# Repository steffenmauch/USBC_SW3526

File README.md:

# USBC_SW3526
ISMARTWARE SW3526 - USB-C PD Charger with I2C interface

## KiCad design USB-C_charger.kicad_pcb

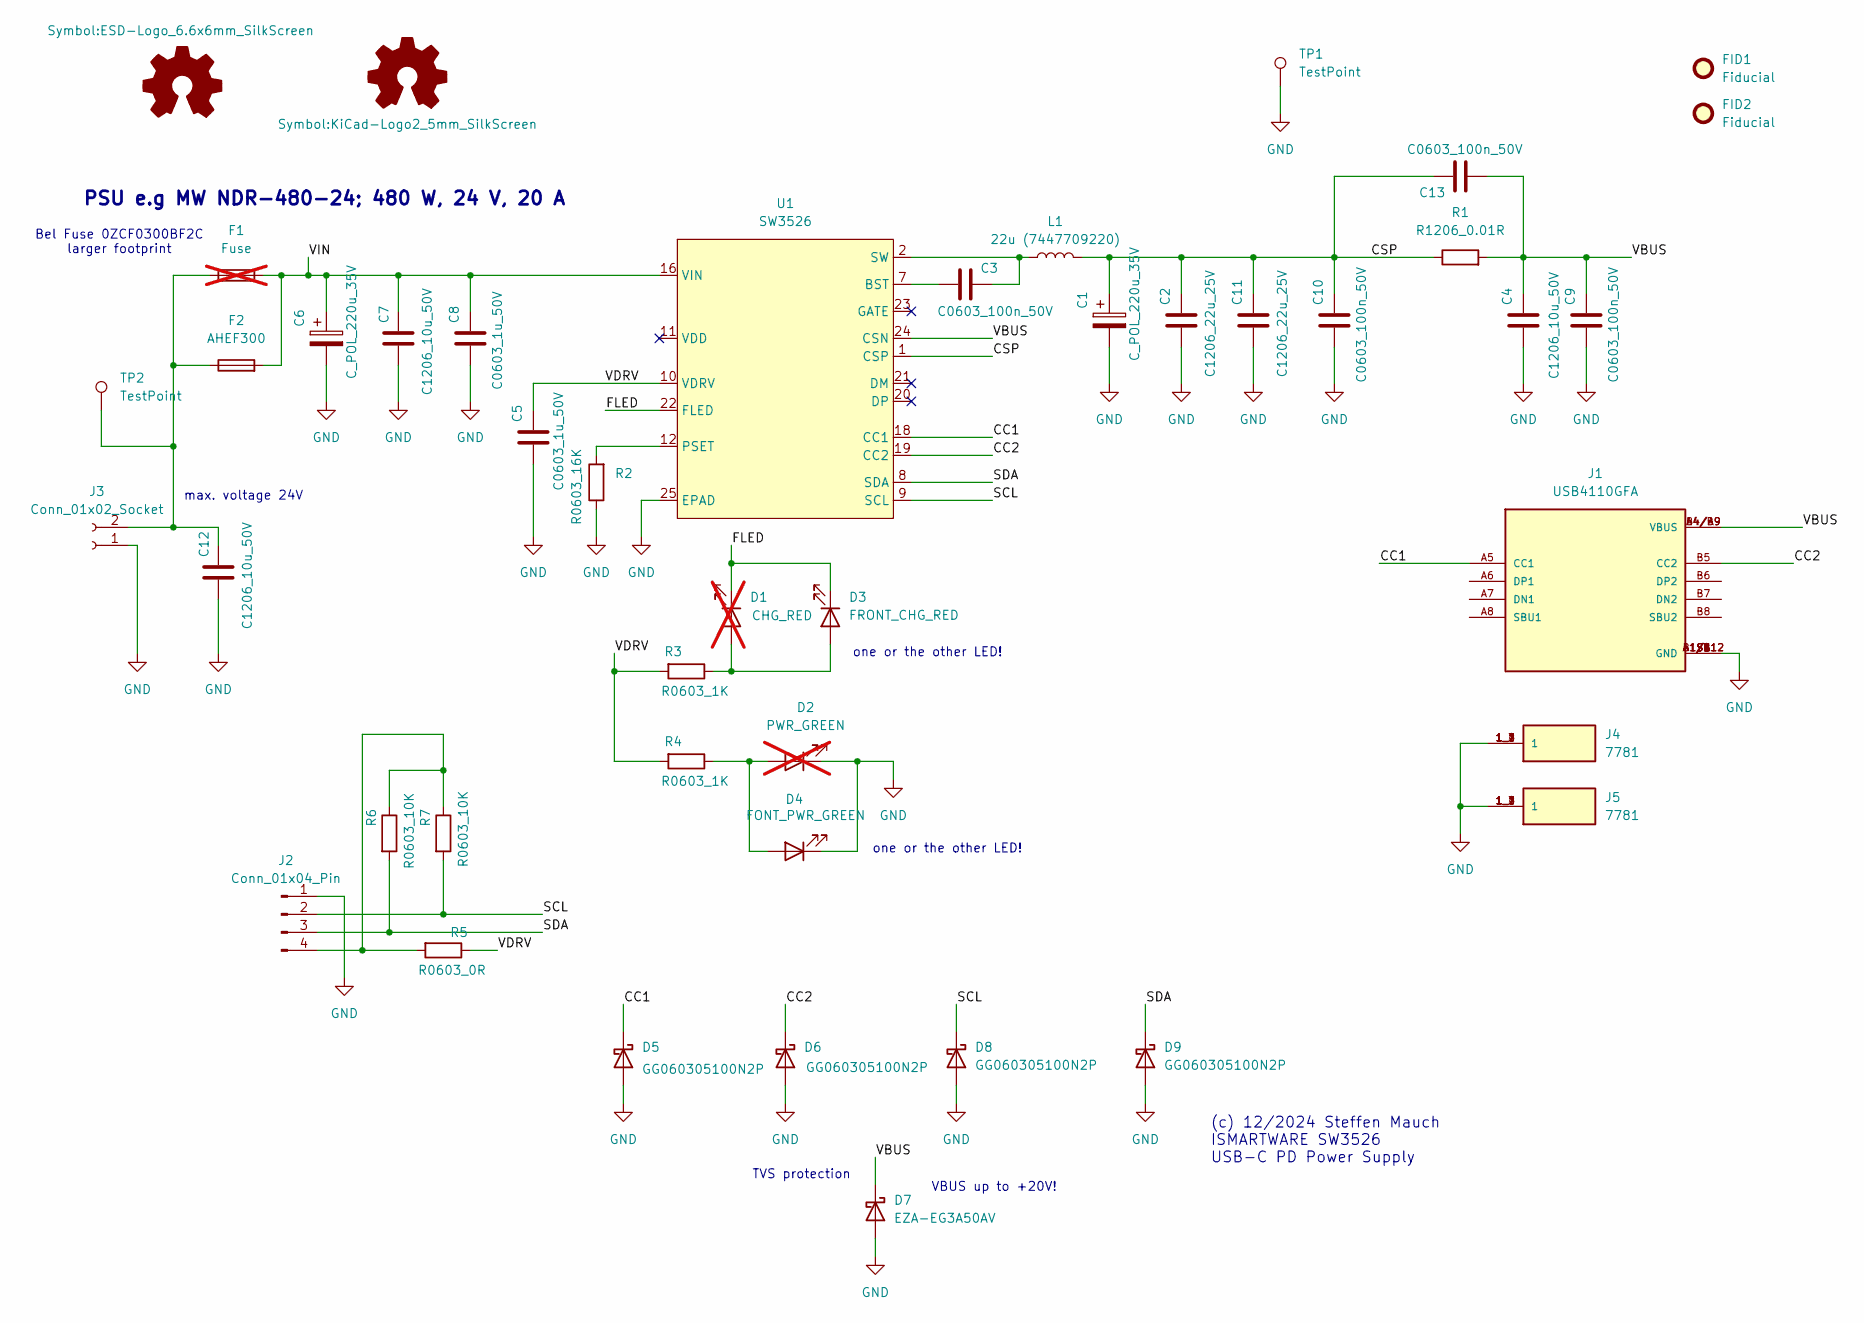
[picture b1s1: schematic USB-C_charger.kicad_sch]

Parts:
C1, C6: C_POL_220u_35V; CP_Elec_8x10.5; MPN EMZL350ARA221MHA0G
C2, C11: C1206_22u_25V; C_1206_3216Metric
C3, C9, C10, C13: C0603_100n_50V; C_0603_1608Metric; MPN CL10B104KB8NNNC
C4, C7, C12: C1206_10u_50V; C_1206_3216Metric
C5, C8: C0603_1u_50V; C_0603_1608Metric
D1: CHG_RED; LED_0603_1608Metric; not fitted
D2: PWR_GREEN; LED_0603_1608Metric; not fitted
D3: FRONT_CHG_RED; WP934RS; MPN WP934RS/ID
D4: FONT_PWR_GREEN; WP934RS; MPN WP934RS/GD
D5, D6, D8, D9: GG060305100N2P; D_0603_1608Metric
D7: EZA-EG3A50AV; D_0603_1608Metric
F1: Fuse; Fuse_2512_6332Metric; not fitted
F2: AHEF300; FUSE_AHEF300_LTF; MPN AHEF300
FID1, FID2: Fiducial; Fiducial_1.5mm_Mask3mm
J1: USB4110GFA; GCT_USB4110GFA; MPN USB4110GFA
J2: Conn_01x04_Pin; JST_XH_B4B-XH-AM_1x04_P2.50mm_Vertical; MPN JST XH4P ST
J3: Conn_01x02_Socket; PhoenixContact_MSTBA_2,5_2-G-5,08_1x02_P5.08mm_Horizontal; MPN MSTBA_2,5_2-G-5,08
J4, J5: 7781; KEYSTONE_7781; MPN 7781
L1: 22u (7447709220); WE-PD_1210; MPN 7447709220
R1: R1206_0.01R; R_1206_3216Metric; MPN PCS1206DR0100ET
R2: R0603_16K; R_0603_1608Metric
R3, R4: R0603_1K; R_0603_1608Metric
R5: R0603_0R; R_0603_1608Metric
R6, R7: R0603_10K; R_0603_1608Metric
SYM1: Logo_Open_Hardware_Small; ESD-Logo_6.6x6mm_SilkScreen
SYM2: Logo_Open_Hardware_Small; KiCad-Logo2_5mm_SilkScreen
TP1, TP2: TestPoint; Pin_D1.0mm_L10.0mm
U1: SW3526; QFN-24-1EP_4x4mm_P0.5mm_EP2.5x2.5mm; MPN SW3526

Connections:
/CC1: D5.1 (K), J1.A5 (CC1), U1.18 (CC1)
/CC2: D6.1 (K), J1.B5 (CC2), U1.19 (CC2)
/CSP: C1.1, C2.2, C10.2, C11.2, C13.2, L1.2, R1.1, U1.1 (CSP)
/FLED: D1.1 (K), D3.1 (K), U1.22 (FLED)
/SCL: D8.1 (K), J2.2, R7.2, U1.9 (SCL)
/SDA: D9.1 (K), J2.3, R6.2, U1.8 (SDA)
/VBUS: C4.2, C9.2, C13.1, D7.1 (K), J1.A4/B9 (VBUS), J1.B4/A9 (VBUS), R1.2, U1.24 (CSN)
/VDRV: C5.2, R3.2, R4.2, R5.1, U1.10 (VDRV)
GND: C1.2, C2.1, C4.1, C5.1, C6.2, C7.1, C8.1, C9.1, C10.1, C11.1, C12.1, D2.1 (K), D4.1 (K), D5.2 (A), D6.2 (A), D7.2 (A), D8.2 (A), D9.2 (A), J1.A1/B12 (GND), J1.B1/A12 (GND), J1.S1 (GND), J1.S2 (GND), J1.S3 (GND), J1.S4 (GND), J2.1, J3.1, J4.1_1 (1), J4.1_2 (1), J4.1_3 (1), J4.1_4 (1), J5.1_1 (1), J5.1_2 (1), J5.1_3 (1), J5.1_4 (1), R2.1, TP1.1, U1.25 (EPAD)
unnamed: C3.2, L1.1, U1.2 (SW), U1.3 (SW), U1.4 (SW), U1.5 (SW), U1.6 (SW)
unnamed: D1.2 (A), D3.2 (A), R3.1
unnamed: D2.2 (A), D4.2 (A), R4.1
unnamed: J2.4, R5.2, R6.1, R7.1
unnamed: C12.2, F1.1, F2.1, J3.2, TP2.1
unnamed: C3.1, U1.7 (BST)
unnamed: R2.2, U1.12 (PSET)
VIN: C6.1, C7.2, C8.2, F1.2, F2.2, U1.13 (VIN), U1.14 (VIN), U1.15 (VIN), U1.16 (VIN)

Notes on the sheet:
Bel Fuse 0ZCF0300BF2C larger footprint
PSU e.g MW NDR-480-24; 480 W, 24 V, 20 A
one or the other LED!
TVS protection
max. voltage 24V
(c) 12/2024 Steffen Mauch ISMARTWARE SW3526 USB-C PD Power Supply
VBUS up to +20V!

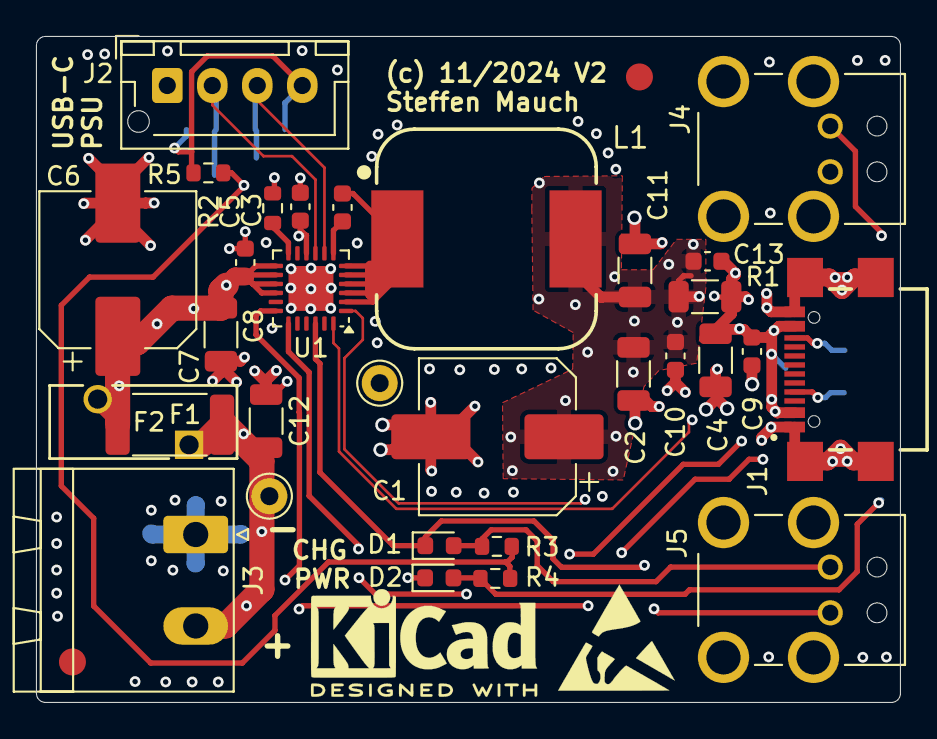
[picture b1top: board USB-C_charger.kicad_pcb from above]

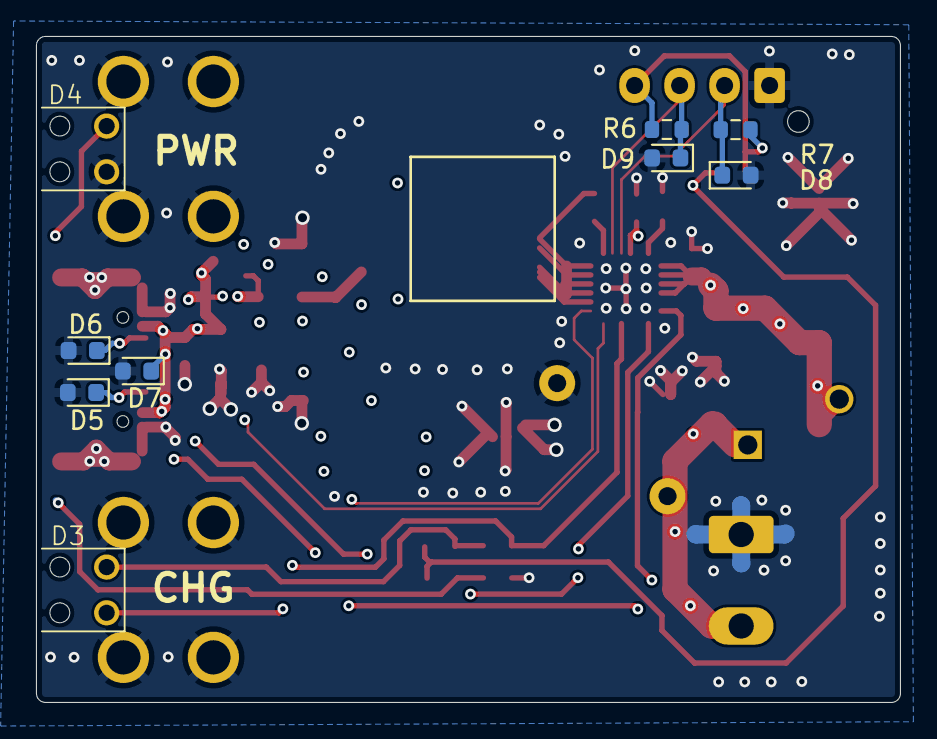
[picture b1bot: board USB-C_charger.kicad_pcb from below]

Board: 4 copper layers, 48.0 x 37.0 mm, 44 parts (9 on the bottom side), 17 nets.

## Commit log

2025-01-16 adding USB-C PD charger KiCAD project for SW3526 IC
2025-03-18 fixing 3D model
